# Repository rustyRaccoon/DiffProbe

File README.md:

# DiffProbe
 High Voltage differential probe for a scope running on 5V USB

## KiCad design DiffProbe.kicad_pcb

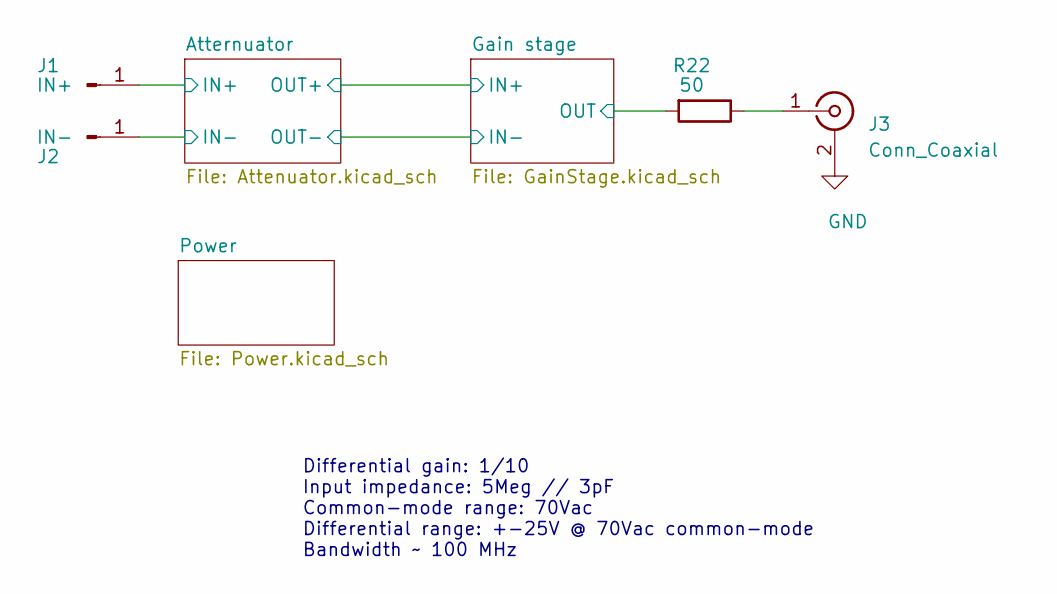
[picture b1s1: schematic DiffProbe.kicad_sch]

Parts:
J1: IN+; PinHeader_1x01_P2.54mm_Horizontal
J2: IN-; PinHeader_1x01_P2.54mm_Horizontal
J3: Conn_Coaxial; SMA_Samtec_SMA-J-P-X-ST-EM1_EdgeMount
R22: 50; R_0603_1608Metric

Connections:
/Atternuator/IN+: J1.1; also elsewhere on the board
/Atternuator/IN-: J2.1; also elsewhere on the board
/Gain stage/OUT: R22.2; also elsewhere on the board
GND: J3.2 (Ext); also elsewhere on the board
unnamed: J3.1 (In), R22.1

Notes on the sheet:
Differential gain: 1/10 Input impedance: 5Meg // 3pF Common-mode range: 70Vac Differential range: +-25V @ 70Vac common-mode Bandwidth ~ 100 MHz

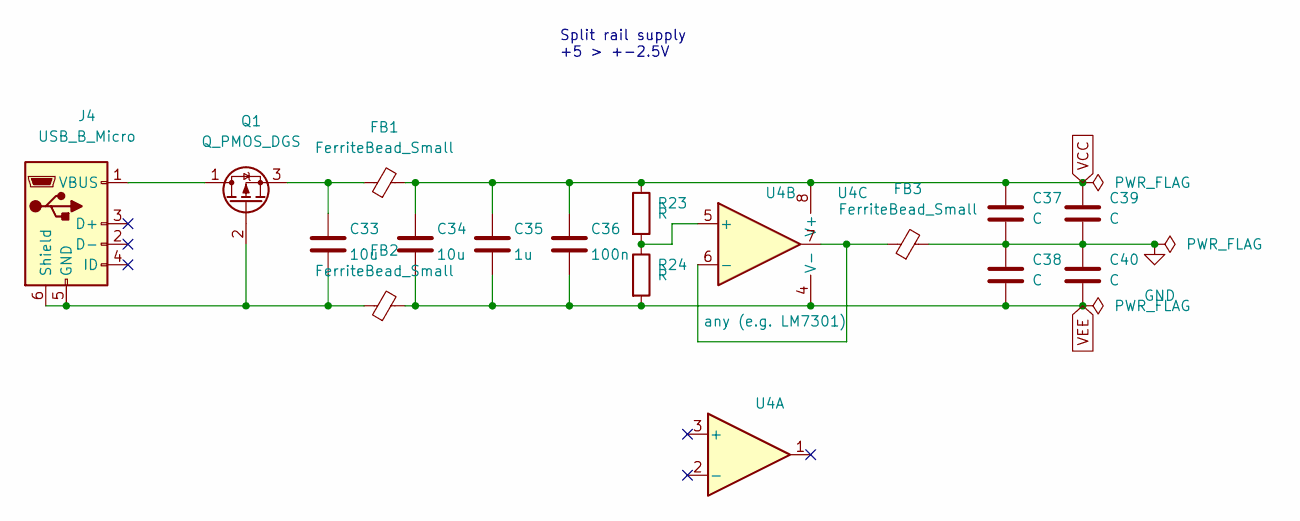
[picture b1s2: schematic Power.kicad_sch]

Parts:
C33, C34: 10u; C_0603_1608Metric
C35: 1u; C_0603_1608Metric
C36: 100n; C_0603_1608Metric
C37, C38, C39, C40: C; C_0603_1608Metric
FB1, FB2, FB3: FerriteBead_Small; L_0603_1608Metric
J4: USB_B_Micro; USB_Micro-AB_Molex_47590-0001
Q1: Q_PMOS_DGS; TSOT-23
R23, R24: R; R_0603_1608Metric
U4: any (e.g. LM7301); MSOP-8_3x3mm_P0.65mm

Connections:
GND: C37.2, C38.1, C39.2, C40.1, FB3.2; also elsewhere on the board
unnamed: C33.2, FB2.1, J4.5 (GND), J4.6 (Shield), Q1.2 (G)
unnamed: J4.1 (VBUS), Q1.1 (D)
unnamed: C33.1, FB1.1, Q1.3 (S)
unnamed: R23.2, R24.1, U4.5 (+)
unnamed: FB3.1, U4.6 (-), U4.7
VCC: C34.1, C35.1, C36.1, C37.1, C39.1, FB1.2, R23.1, U4.8 (V+); also elsewhere on the board
VEE: C34.2, C35.2, C36.2, C38.2, C40.2, FB2.2, R24.2, U4.4 (V-); also elsewhere on the board

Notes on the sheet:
Split rail supply +5 > +-2.5V

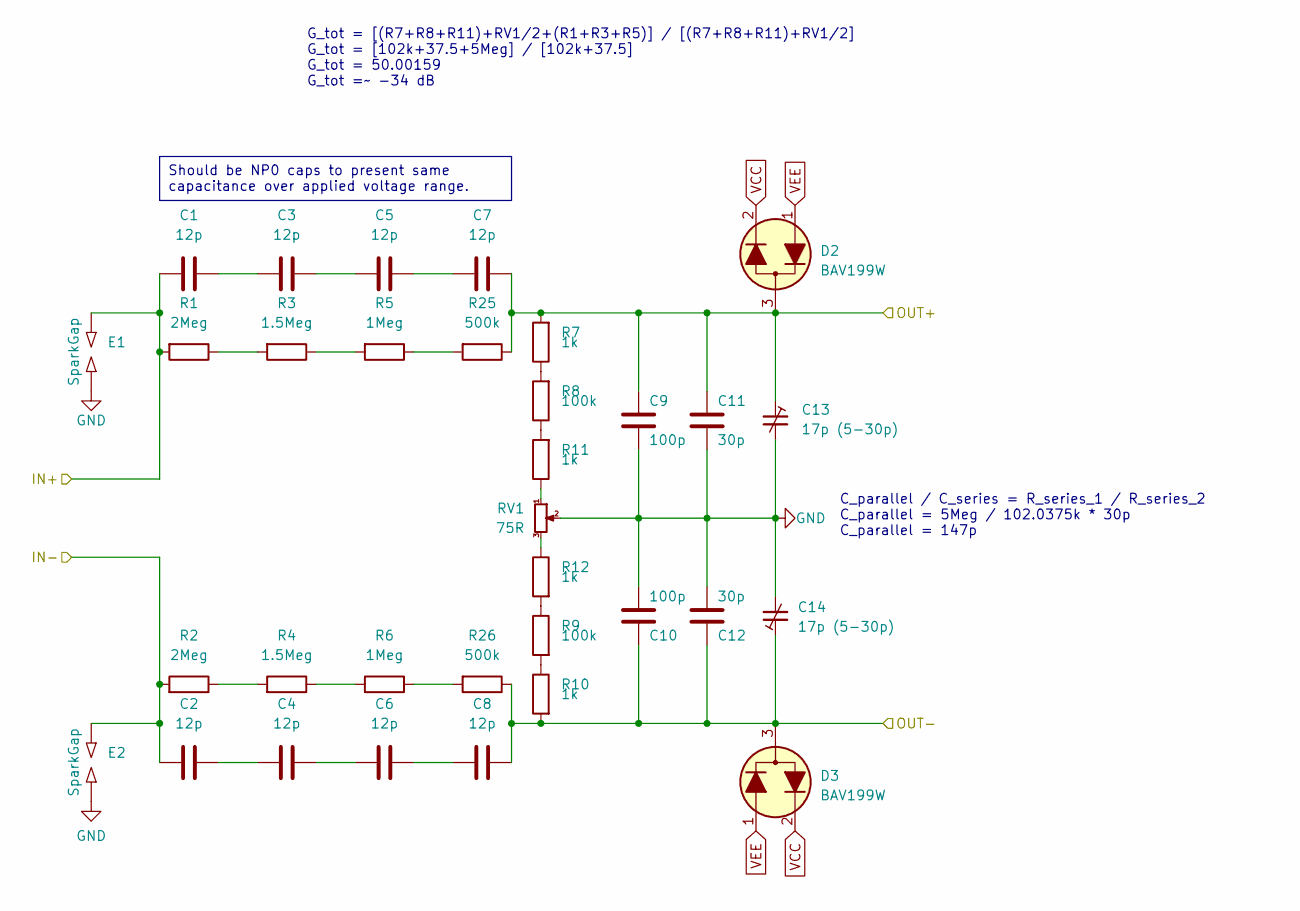
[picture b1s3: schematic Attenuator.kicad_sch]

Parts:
C1, C2, C3, C4, C5, C6, C7, C8: 12p; C_0603_1608Metric
C9, C10: 100p; C_0603_1608Metric
C11, C12: 30p; C_0603_1608Metric
C13, C14: 17p (5-30p); C_Trimmer_Murata_TZB4-A
D2, D3: BAV199W; SC-70
E1, E2: SparkGap; Spark_Gap_1.65x1.1
R1, R2: 2Meg; R_0603_1608Metric
R3, R4: 1.5Meg; R_0603_1608Metric
R5, R6: 1Meg; R_0603_1608Metric
R7, R10, R11, R12: 1k; R_0603_1608Metric
R8, R9: 100k; R_0603_1608Metric
R25, R26: 500k; R_0603_1608Metric
RV1: 75R; Potentiometer_Bourns_3214W_Vertical

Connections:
/Atternuator/IN+: C1.2, E1.1, R1.2; also elsewhere on the board
/Atternuator/IN-: C2.2, E2.1, R2.2; also elsewhere on the board
/Atternuator/OUT+: C7.1, C9.1, C11.1, C13.1, D2.3 (C), R7.2, R25.1; also elsewhere on the board
/Atternuator/OUT-: C8.1, C10.1, C12.1, C14.1, D3.3 (C), R10.2, R26.1; also elsewhere on the board
GND: C9.2, C10.2, C11.2, C12.2, C13.2, C14.2, E1.2, E2.2, RV1.2; also elsewhere on the board
unnamed: C1.1, C3.2
unnamed: C2.1, C4.2
unnamed: C3.1, C5.2
unnamed: C4.1, C6.2
unnamed: C5.1, C7.2
unnamed: C6.1, C8.2
unnamed: R1.1, R3.2
unnamed: R2.1, R4.2
unnamed: R3.1, R5.2
unnamed: R4.1, R6.2
unnamed: R7.1, R8.2
unnamed: R9.2, R10.1
unnamed: R11.1, RV1.1
unnamed: R8.1, R11.2
unnamed: R12.1, RV1.3
unnamed: R9.1, R12.2
unnamed: R5.1, R25.2
unnamed: R6.1, R26.2
VCC: D2.2 (K), D3.2 (K); also elsewhere on the board
VEE: D2.1 (A), D3.1 (A); also elsewhere on the board

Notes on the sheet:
Should be NP0 caps to present same capacitance over applied voltage range.
C_parallel / C_series = R_series_1 / R_series_2 C_parallel = 5Meg / 102.0375k * 30p C_parallel = 147p
G_tot = [(R7+R8+R11)+RV1/2+(R1+R3+R5)] / [(R7+R8+R11)+RV1/2] G_tot = [102k+37.5+5Meg] / [102k+37.5] G_tot = 50.00159 G_tot =~ -34 dB

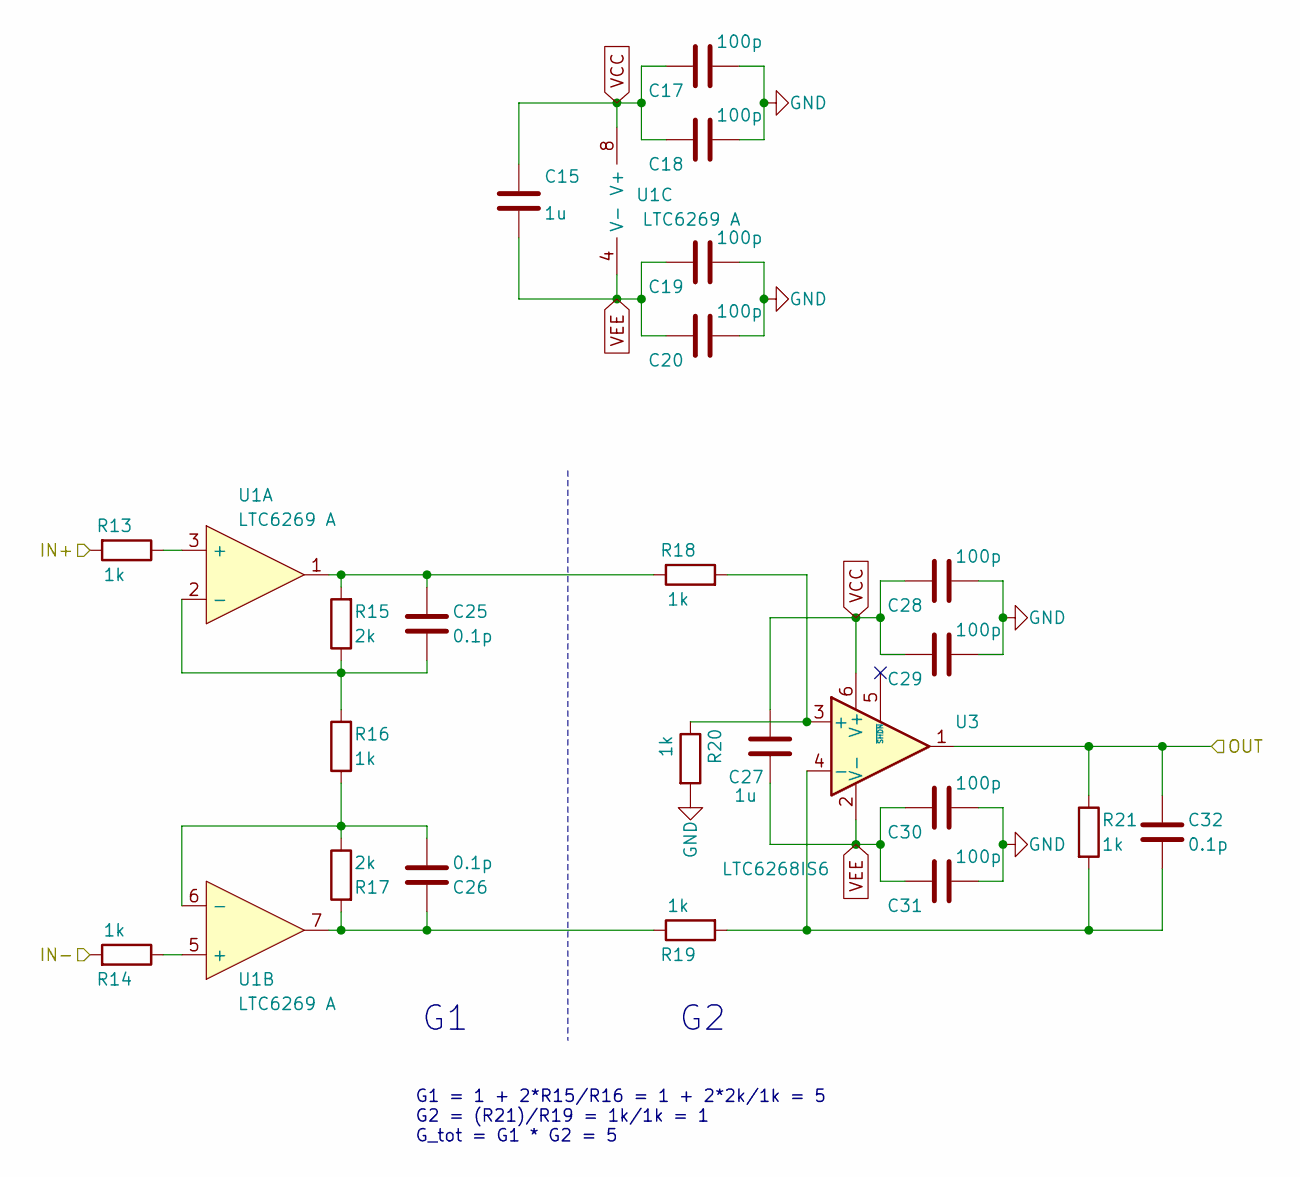
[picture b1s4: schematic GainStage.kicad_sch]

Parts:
C15, C27: 1u; C_0603_1608Metric
C17, C18, C19, C20, C28, C29, C30, C31: 100p; C_0603_1608Metric
C25, C26, C32: 0.1p; C_0603_1608Metric
R13, R14, R16, R18, R19, R20, R21: 1k; R_0603_1608Metric
R15, R17: 2k; R_0603_1608Metric
U1: LTC6269 A; MSOP-8-1EP_3x3mm_P0.65mm_EP1.68x1.88mm
U3: LTC6268IS6; TSOT-23-6

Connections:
/Atternuator/OUT+: R13.2; also elsewhere on the board
/Atternuator/OUT-: R14.2; also elsewhere on the board
/Gain stage/OUT: C32.2, R21.1, U3.1; also elsewhere on the board
GND: C17.1, C18.1, C19.1, C20.1, C28.1, C29.1, C30.1, C31.1, R20.2; also elsewhere on the board
unnamed: C25.1, R15.2, R18.1, U1.1
unnamed: C26.1, R17.2, R19.1, U1.7
unnamed: R13.1, U1.3 (+)
unnamed: C25.2, R15.1, R16.2, U1.2 (-)
unnamed: R14.1, U1.5 (+)
unnamed: C26.2, R16.1, R17.1, U1.6 (-)
unnamed: R18.2, R20.1, U3.3 (+)
unnamed: C32.1, R19.2, R21.2, U3.4 (-)
VCC: C15.1, C17.2, C18.2, C27.1, C28.2, C29.2, U1.8 (V+), U3.6 (V+); also elsewhere on the board
VEE: C15.2, C19.2, C20.2, C27.2, C30.2, C31.2, U1.4 (V-), U1.9 (V-), U3.2 (V-); also elsewhere on the board

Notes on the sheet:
G1 = 1 + 2*R15/R16 = 1 + 2*2k/1k = 5 G2 = (R21)/R19 = 1k/1k = 1 G_tot = G1 * G2 = 5

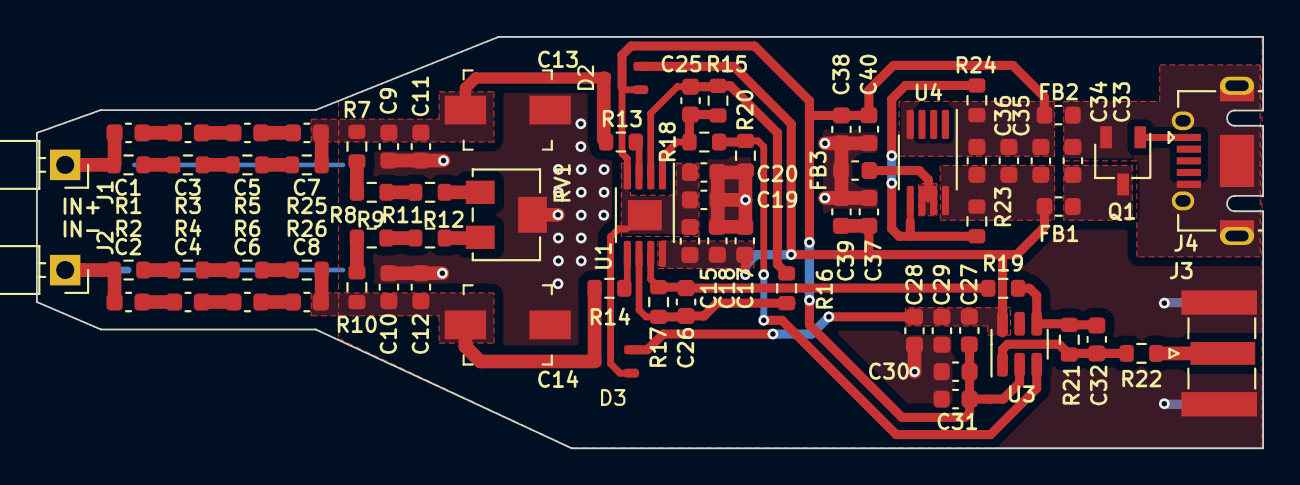
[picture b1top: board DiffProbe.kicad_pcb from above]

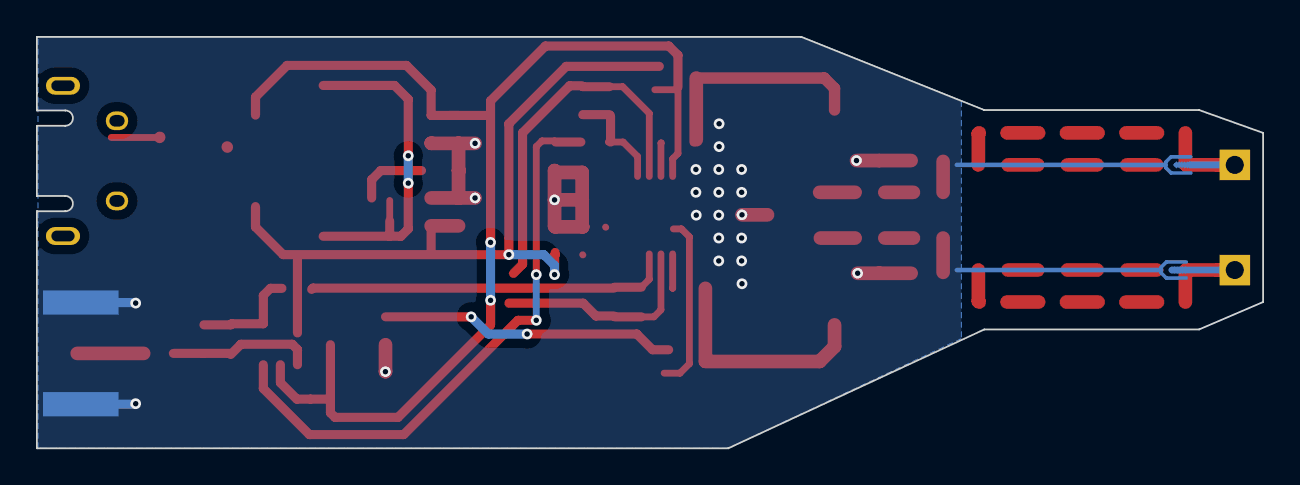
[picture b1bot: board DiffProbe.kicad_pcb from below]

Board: 2 copper layers, 68.1 x 22.9 mm, 77 parts (2 on the bottom side), 40 nets.

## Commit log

2023-03-25 Routed PCB
